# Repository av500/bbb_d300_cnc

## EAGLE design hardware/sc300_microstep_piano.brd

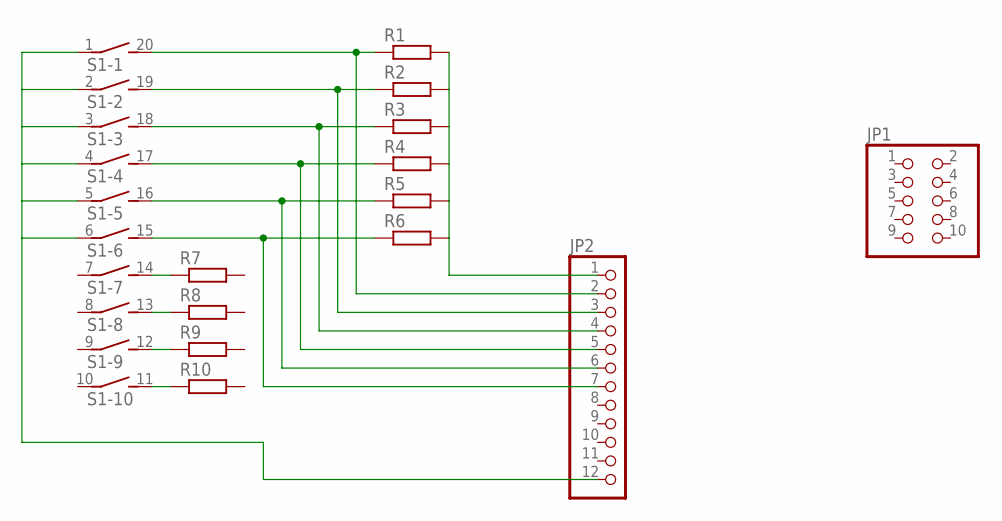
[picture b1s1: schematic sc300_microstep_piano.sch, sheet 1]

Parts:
JP1: PINHD-2X5; 2X05
JP2: PINHD-1X12; 1X12
R1, R2, R3, R4, R5, R6, R7, R8, R9, R10: R-EU_0603; R0603
S1: DIP10SB

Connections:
GND_SC: JP2.12, S1.1, S1.2 (1), S1.3 (1), S1.4 (1), S1.5 (1), S1.6 (1)
unnamed: R7.1, S1.14 (2)
unnamed: JP2.2, R1.1, S1.20 (2)
unnamed: R8.1, S1.13 (2)
unnamed: JP2.3, R2.1, S1.19 (2)
unnamed: JP2.4, R3.1, S1.18 (2)
unnamed: JP2.5, R4.1, S1.17 (2)
unnamed: JP2.6, R5.1, S1.16 (2)
unnamed: JP2.7, R6.1, S1.15 (2)
unnamed: R9.1, S1.12 (2)
unnamed: R10.1, S1.11 (2)
unnamed: JP2.1, R1.2, R2.2, R3.2, R4.2, R5.2, R6.2

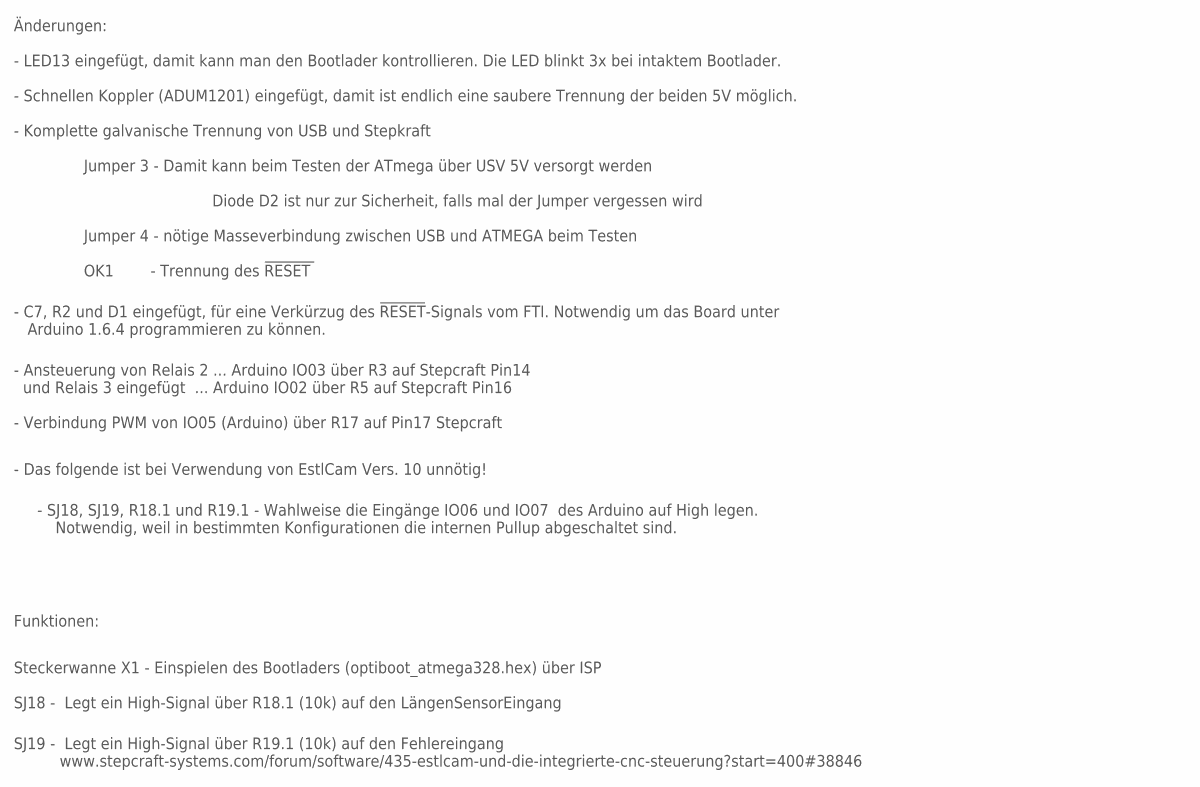
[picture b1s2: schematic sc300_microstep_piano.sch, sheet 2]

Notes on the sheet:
Änderungen:
- LED13 eingefügt, damit kann man den Bootlader kontrollieren. Die LED blinkt 3x bei intaktem Bootlader.
- Schnellen Koppler (ADUM1201) eingefügt, damit ist endlich eine saubere Trennung der beiden 5V möglich.
Jumper 3 - Damit kann beim Testen der ATmega über USV 5V versorgt werden
Diode D2 ist nur zur Sicherheit, falls mal der Jumper vergessen wird
Funktionen:
Steckerwanne X1 - Einspielen des Bootladers (optiboot_atmega328.hex) über ISP
Jumper 4 - nötige Masseverbindung zwischen USB und ATMEGA beim Testen
- Komplette galvanische Trennung von USB und Stepkraft
- C7, R2 und D1 eingefügt, für eine Verkürzug des !RESET!-Signals vom FTI. Notwendig um das Board unter Arduino 1.6.4 programmieren zu können.
OK1 - Trennung des !RESET
- Ansteuerung von Relais 2 ... Arduino IO03 über R3 auf Stepcraft Pin14 und Relais 3 eingefügt ... Arduino IO02 über R5 auf Stepcraft Pin16
- Verbindung PWM von IO05 (Arduino) über R17 auf Pin17 Stepcraft
SJ19 - Legt ein High-Signal über R19.1 (10k) auf den Fehlereingang www.stepcraft-systems.com/forum/software/435-estlcam-und-die-integrierte-cnc-steuerung?start=400#38846
SJ18 - Legt ein High-Signal über R18.1 (10k) auf den LängenSensorEingang
- SJ18, SJ19, R18.1 und R19.1 - Wahlweise die Eingänge IO06 und IO07 des Arduino auf High legen. Notwendig, weil in bestimmten Konfigurationen die internen Pullup abgeschaltet sind.
- Das folgende ist bei Verwendung von EstlCam Vers. 10 unnötig!

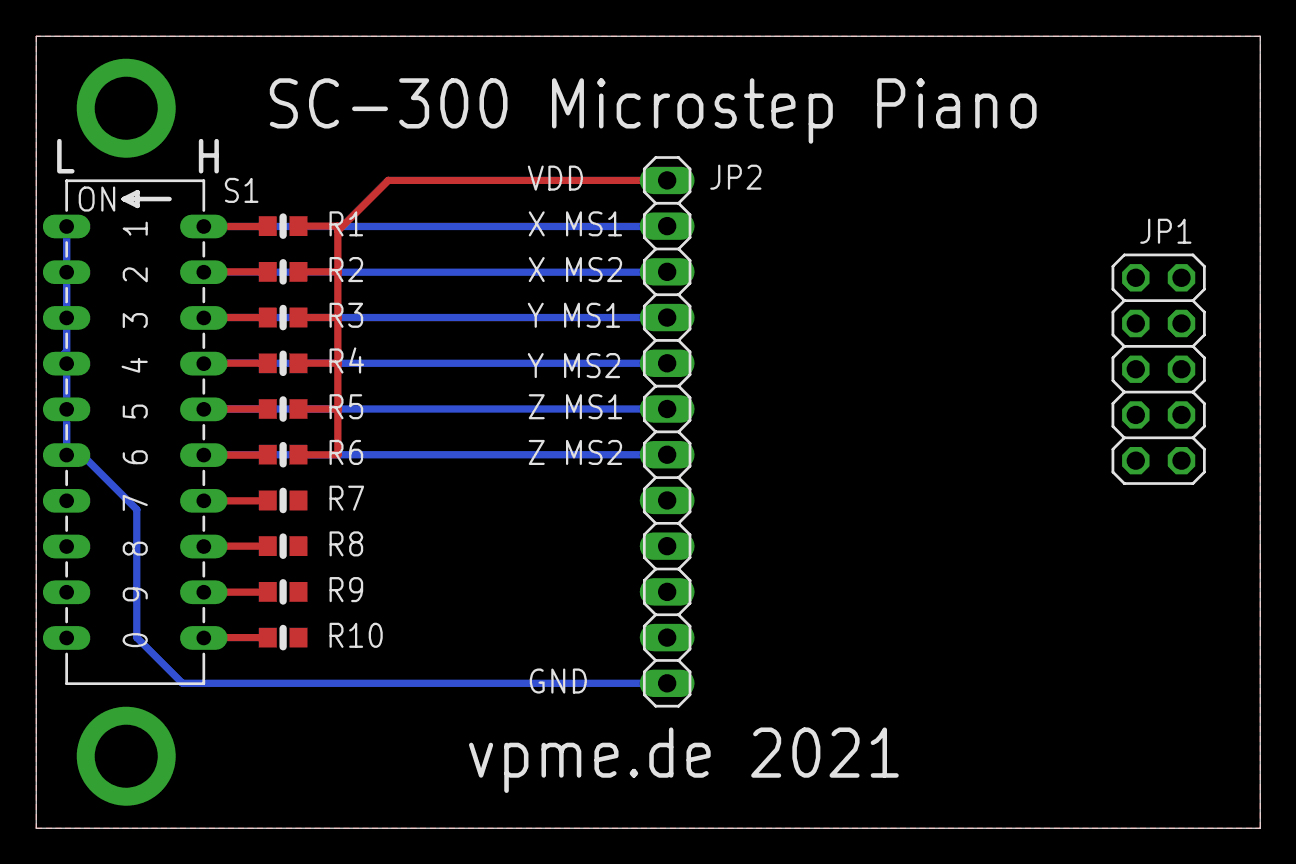
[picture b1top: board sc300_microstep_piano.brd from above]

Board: 2 copper layers, 68.0 x 44.0 mm, 13 parts (0 on the bottom side), 12 nets.

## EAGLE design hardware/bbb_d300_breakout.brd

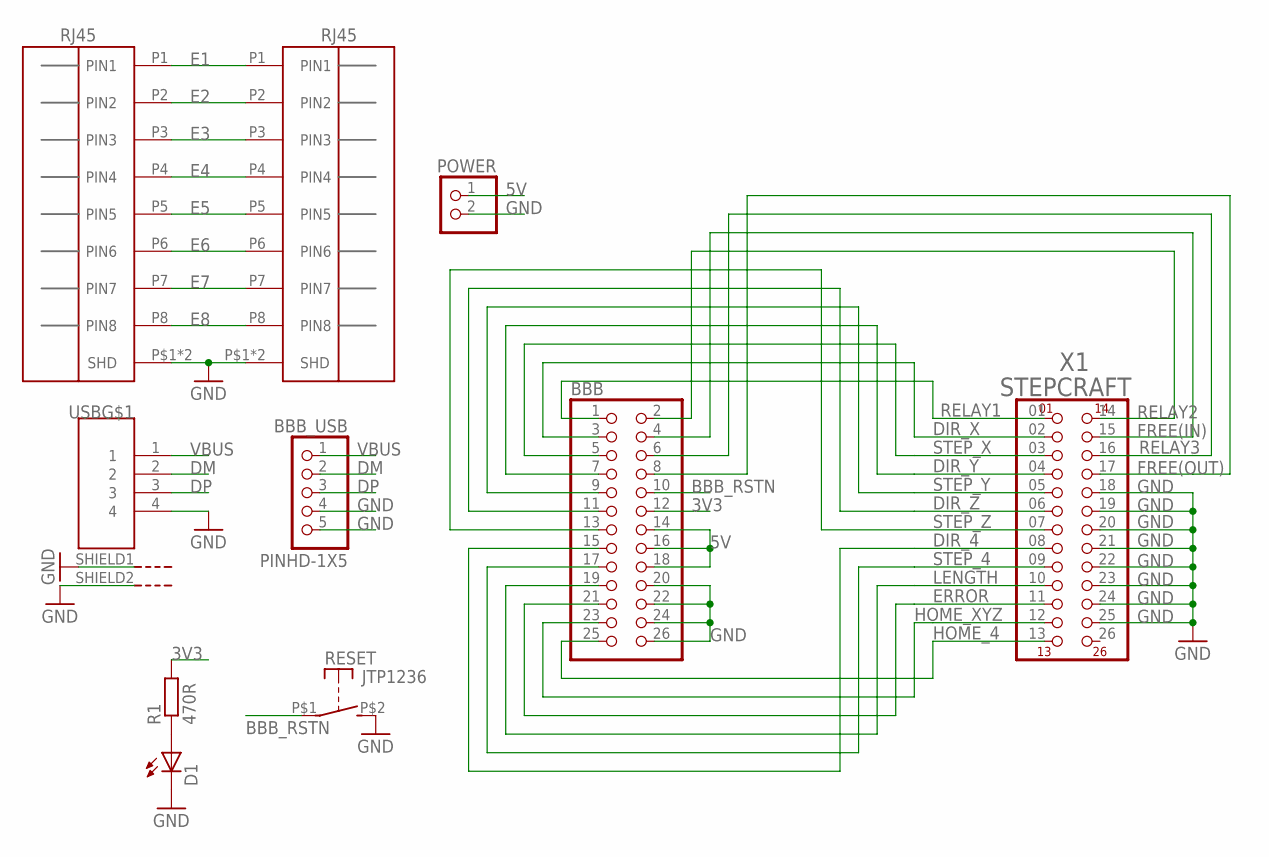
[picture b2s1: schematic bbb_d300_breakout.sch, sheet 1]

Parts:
BBB: PINHD-2X13; 2X13
BBB_USB: PINHD-1X5; 1X05_XXL
D1: LEDXXL; LED3MM_XXL
POWER: PINHD-1X2; 1X02
R1: 470R; R0805
RESET: JTP1236
USB: USB_HOST; USB
X1: STEPCRAFT; 2X13_90_STEPCRAFT
X2, X3: RJ45

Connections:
3V3: BBB.12, R1.2
5V: BBB.14, BBB.16, BBB.18, POWER.1
BBB_RSTN: BBB.10, RESET.P$1
DIR_4: BBB.15, X1.08 (8)
DIR_X: BBB.3, X1.02 (2)
DIR_Y: BBB.7, X1.04 (4)
DIR_Z: BBB.11, X1.06 (6)
DM: BBB_USB.2, USB.2
DP: BBB_USB.3, USB.3
E1: X2.P1 (PIN1), X3.P1 (PIN1)
E2: X2.P2 (PIN2), X3.P2 (PIN2)
E3: X2.P3 (PIN3), X3.P3 (PIN3)
E4: X2.P4 (PIN4), X3.P4 (PIN4)
E5: X2.P5 (PIN5), X3.P5 (PIN5)
E6: X2.P6 (PIN6), X3.P6 (PIN6)
E7: X2.P7 (PIN7), X3.P7 (PIN7)
E8: X2.P8 (PIN8), X3.P8 (PIN8)
ERROR: BBB.21, X1.11
FREE(IN): BBB.4, X1.15
FREE(OUT): BBB.8, X1.17
GND: BBB.20, BBB.22, BBB.24, BBB.26, BBB_USB.4, BBB_USB.5, D1.K (C), POWER.2, RESET.P$2 (S), USB.4, USB.SHIELD1 (G), USB.SHIELD2 (G), X1.18, X1.19, X1.20, X1.21, X1.22, X1.23, X1.24, X1.25, X2.P$1 (SHD), X2.P$2 (SHD), X3.P$1 (SHD), X3.P$2 (SHD)
HOME_4: BBB.25, X1.13
HOME_XYZ: BBB.23, X1.12
LENGTH: BBB.19, X1.10
unnamed: D1.A, R1.1
RELAY1: BBB.1, X1.01 (1)
RELAY2: BBB.2, X1.14
RELAY3: BBB.6, X1.16
STEP_4: BBB.17, X1.09 (9)
STEP_X: BBB.5, X1.03 (3)
STEP_Y: BBB.9, X1.05 (5)
STEP_Z: BBB.13, X1.07 (7)
VBUS: BBB_USB.1, USB.1

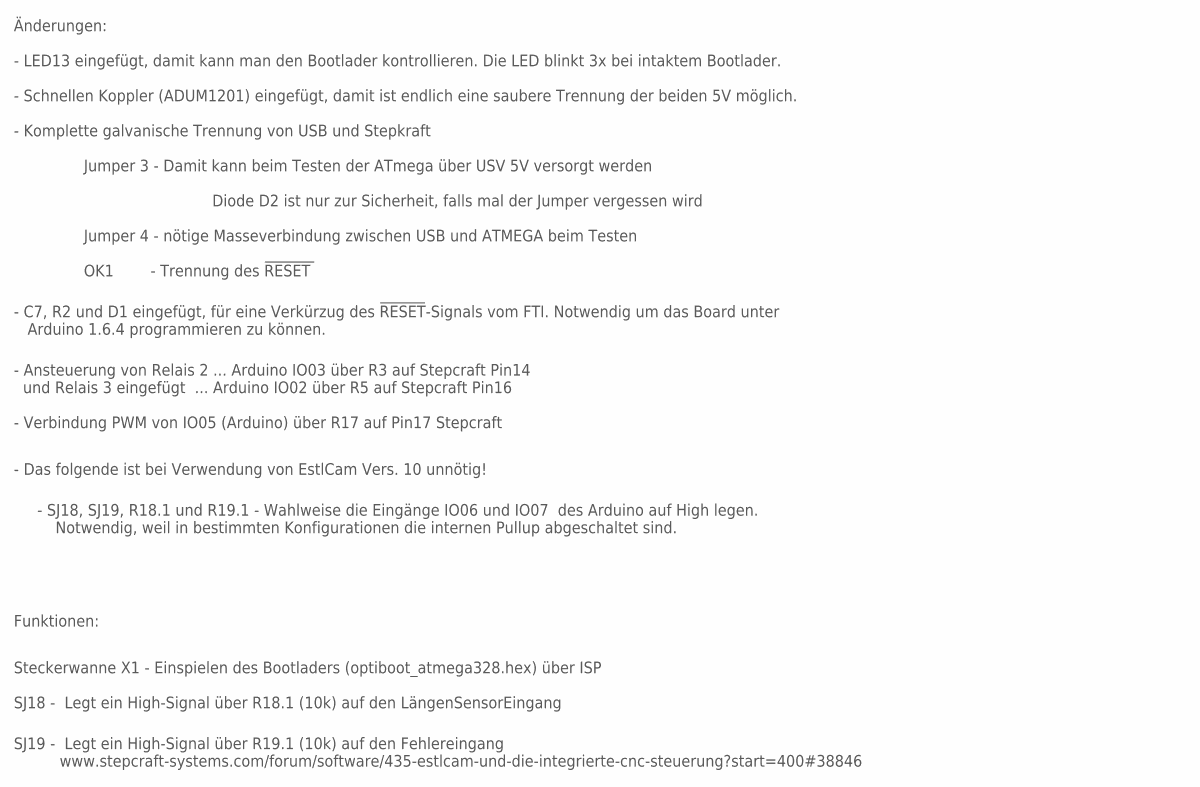
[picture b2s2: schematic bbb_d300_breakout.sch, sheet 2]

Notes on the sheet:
Änderungen:
- LED13 eingefügt, damit kann man den Bootlader kontrollieren. Die LED blinkt 3x bei intaktem Bootlader.
- Schnellen Koppler (ADUM1201) eingefügt, damit ist endlich eine saubere Trennung der beiden 5V möglich.
Jumper 3 - Damit kann beim Testen der ATmega über USV 5V versorgt werden
Diode D2 ist nur zur Sicherheit, falls mal der Jumper vergessen wird
Funktionen:
Steckerwanne X1 - Einspielen des Bootladers (optiboot_atmega328.hex) über ISP
Jumper 4 - nötige Masseverbindung zwischen USB und ATMEGA beim Testen
- Komplette galvanische Trennung von USB und Stepkraft
- C7, R2 und D1 eingefügt, für eine Verkürzug des !RESET!-Signals vom FTI. Notwendig um das Board unter Arduino 1.6.4 programmieren zu können.
OK1 - Trennung des !RESET
- Ansteuerung von Relais 2 ... Arduino IO03 über R3 auf Stepcraft Pin14 und Relais 3 eingefügt ... Arduino IO02 über R5 auf Stepcraft Pin16
- Verbindung PWM von IO05 (Arduino) über R17 auf Pin17 Stepcraft
SJ19 - Legt ein High-Signal über R19.1 (10k) auf den Fehlereingang www.stepcraft-systems.com/forum/software/435-estlcam-und-die-integrierte-cnc-steuerung?start=400#38846
SJ18 - Legt ein High-Signal über R18.1 (10k) auf den LängenSensorEingang
- SJ18, SJ19, R18.1 und R19.1 - Wahlweise die Eingänge IO06 und IO07 des Arduino auf High legen. Notwendig, weil in bestimmten Konfigurationen die internen Pullup abgeschaltet sind.
- Das folgende ist bei Verwendung von EstlCam Vers. 10 unnötig!

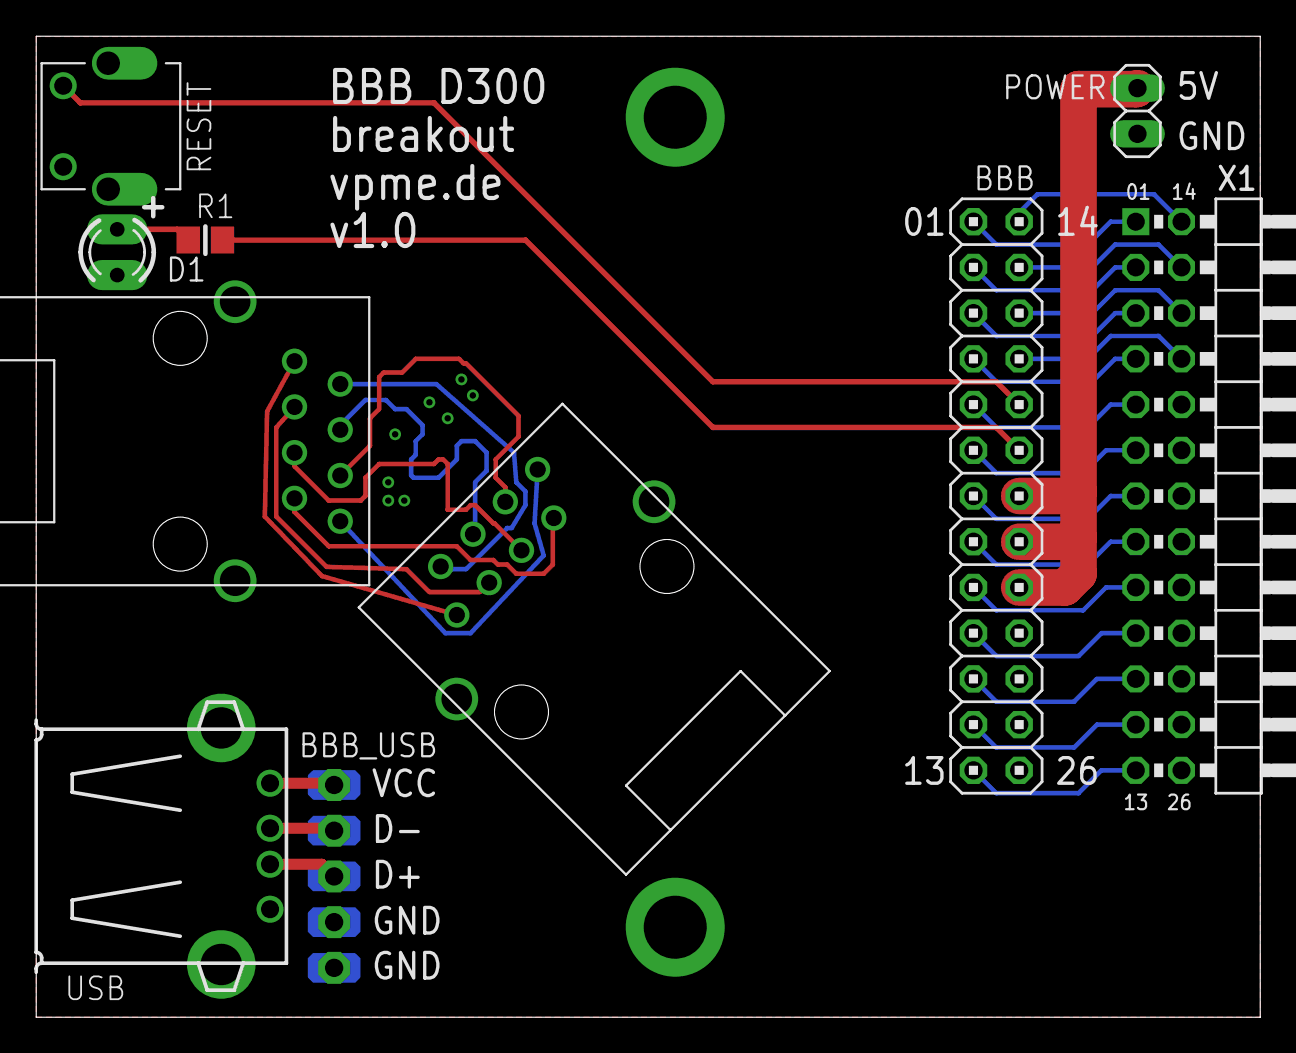
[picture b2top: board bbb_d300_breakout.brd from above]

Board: 2 copper layers, 68.0 x 54.5 mm, 10 parts (0 on the bottom side), 33 nets.

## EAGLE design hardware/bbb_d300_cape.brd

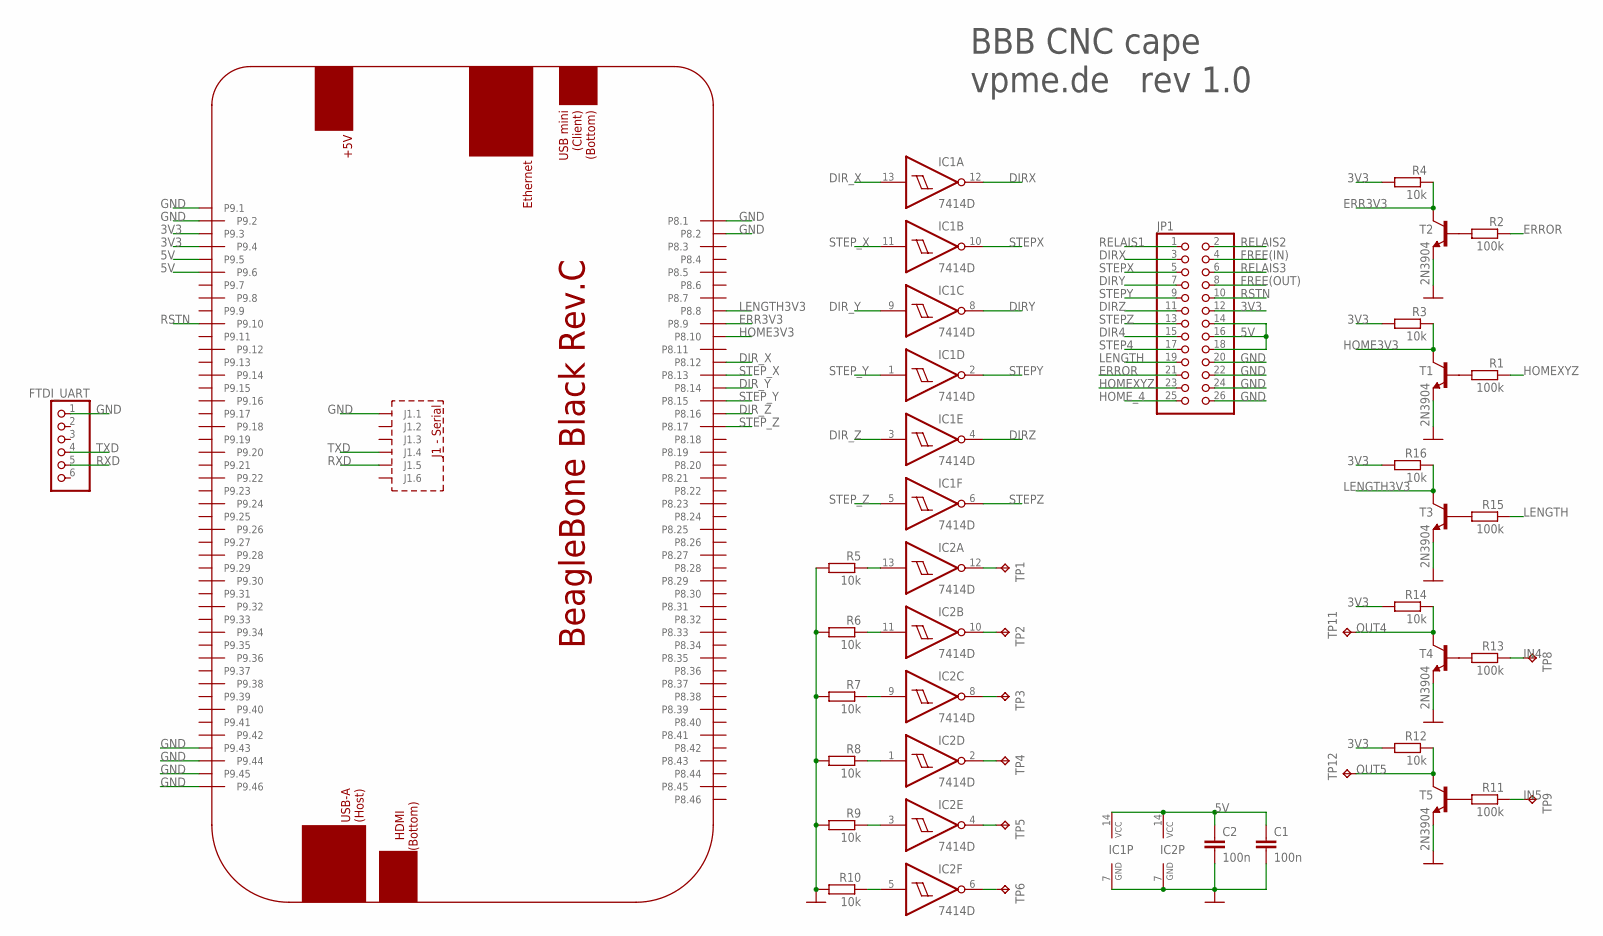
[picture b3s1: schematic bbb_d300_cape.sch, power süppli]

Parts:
C1, C2: 100n; C0603
FTDI_UART: PINHD-1X6/90; 1X06/90
IC1, IC2: 7414D; SO14
JP1: PINHD-2X13/90; 2X13/90
PCB2: BEAGLEBONE_BLACK_CAPE
R1, R2, R11, R13, R15: 100k; R0603
R3, R4, R5, R6, R7, R8, R9, R10, R12, R14, R16: 10k; R0603
T1, T2, T3, T4, T5: 2N3904; SOT23-BEC
TP1, TP2, TP3, TP4, TP5, TP6, TP8, TP9, TP11, TP12: TPTP12R; TP12R

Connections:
3V3: JP1.12, PCB2.P9.3, PCB2.P9.4, R3.2, R4.2, R12.2, R14.2, R16.2
5V: C1.1, C2.1, IC1.14 (VCC), IC2.14 (VCC), JP1.14, JP1.16, JP1.18, PCB2.P9.5, PCB2.P9.6
DIR4: JP1.15
DIRX: IC1.12 (O), JP1.3
DIRY: IC1.8 (O), JP1.7
DIRZ: IC1.4 (O), JP1.11
DIR_X: IC1.13 (I), PCB2.P8.12
DIR_Y: IC1.9 (I), PCB2.P8.14
DIR_Z: IC1.3 (I), PCB2.P8.16
ERR3V3: PCB2.P8.9, R4.1, T2.C
ERROR: JP1.21, R2.1
FREE(IN): JP1.4
FREE(OUT): JP1.8
GND: C1.2, C2.2, FTDI_UART.1, IC1.7 (GND), IC2.7 (GND), JP1.20, JP1.22, JP1.24, JP1.26, PCB2.J1.1, PCB2.P8.1, PCB2.P8.2, PCB2.P9.1, PCB2.P9.2, PCB2.P9.43, PCB2.P9.44, PCB2.P9.45, PCB2.P9.46, R5.2, R6.2, R7.2, R8.2, R9.2, R10.2, T1.E, T2.E, T3.E, T4.E, T5.E
HOME3V3: PCB2.P8.10, R3.1, T1.C
HOMEXYZ: JP1.23, R1.1
HOME_4: JP1.25
IN4: R13.1, TP8.TP
IN5: R11.1, TP9.TP
LENGTH: JP1.19, R15.1
LENGTH3V3: PCB2.P8.8, R16.1, T3.C
unnamed: IC2.13 (I), R5.1
unnamed: R2.2, T2.B
unnamed: IC2.11 (I), R6.1
unnamed: IC2.9 (I), R7.1
unnamed: IC2.1 (I), R8.1
unnamed: IC2.3 (I), R9.1
unnamed: IC2.5 (I), R10.1
unnamed: IC2.6 (O), TP6.TP
unnamed: IC2.4 (O), TP5.TP
unnamed: IC2.2 (O), TP4.TP
unnamed: IC2.8 (O), TP3.TP
unnamed: IC2.10 (O), TP2.TP
unnamed: IC2.12 (O), TP1.TP
unnamed: R11.2, T5.B
unnamed: R13.2, T4.B
unnamed: R1.2, T1.B
unnamed: R15.2, T3.B
OUT4: R14.1, T4.C, TP11.TP
OUT5: R12.1, T5.C, TP12.TP
RELAIS1: JP1.1
RELAIS2: JP1.2
RELAIS3: JP1.6
RSTN: JP1.10, PCB2.P9.10
RXD: FTDI_UART.5, PCB2.J1.5
STEP4: JP1.17
STEPX: IC1.10 (O), JP1.5
STEPY: IC1.2 (O), JP1.9
STEPZ: IC1.6 (O), JP1.13
STEP_X: IC1.11 (I), PCB2.P8.13
STEP_Y: IC1.1 (I), PCB2.P8.15
STEP_Z: IC1.5 (I), PCB2.P8.17
TXD: FTDI_UART.4, PCB2.J1.4

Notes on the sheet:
BBB CNC cape vpme.de rev 1.0

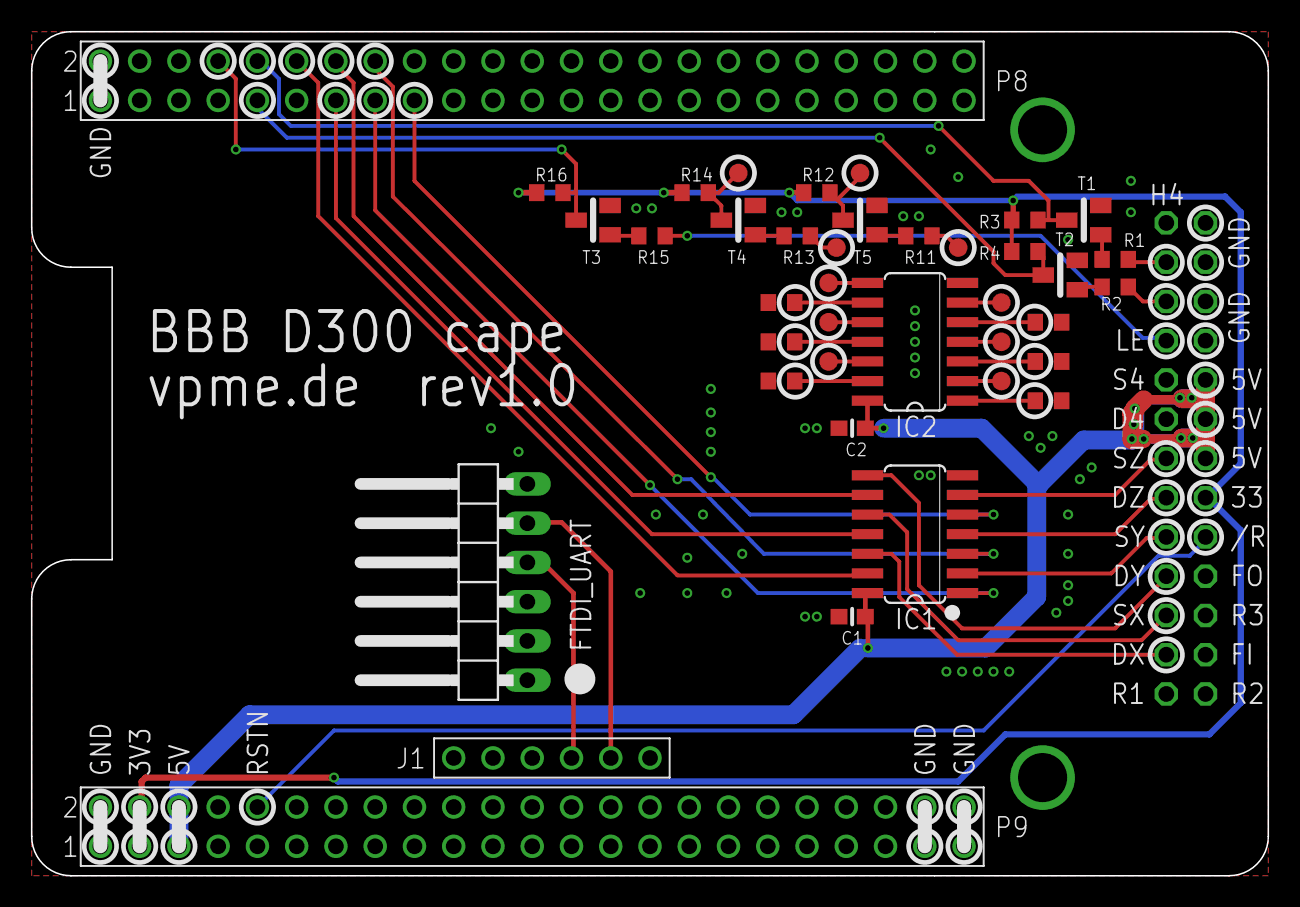
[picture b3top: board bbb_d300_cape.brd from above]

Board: 2 copper layers, 80.0 x 54.6 mm, 38 parts (1 on the bottom side), 45 nets.

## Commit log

2023-03-30 add hardware files
2023-03-30 add the Stepcraft D300 machinekit config (work in progress)
2023-03-30 swap USB and ETH position
2023-03-30 - add tool probing on P811 - fix tool change freeze
2023-03-30 add pinmux for P8 pin 11
2023-03-30 add RS274NGC_STARTUP_CODE section
2023-03-30 clean tool table
2023-03-30 dont track pru-stepper.var in git
2023-03-30 fox tzpo
2023-03-30 connect tool length to P8.08
2023-03-30 update the gerbers
2023-03-30 add images of PCBs
2023-03-31 remove unneeded paths
2023-03-31 add buttons for tool touch off and three place holder for other actions
2023-03-31 edit footprint of RJ45
2023-05-05 add a board that allows to select the microsteps with DIP switches (some soldering required...)
